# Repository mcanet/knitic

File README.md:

Knitic
======

This software is part of the first open hardware knitting machine project, at the moment based on old electronic Brother knitting machines. 

Here we are testing with KH930, KH940, but we will work with any Digital Brother Knitting machine. 

We have developed in an artist residency at Marginalia+Lab in Belo Horizonte (Brazil) and Constant(Belgium). 
There is more information on the project website: http://knitic.com

Authors: Varvara Guljajeva(http://varvarag.info) and Mar Canet (http://mcanet.info). We are a couple of new media artist that we like to build our own tools.

We have publish some articles about this topic:
- Knitic - The Revolution of Soft Digital Fabrication. DH 2013: 497-499 [http://dh2013.unl.edu/abstracts/ab-173.html]

The project copyright with GNU-GPL: http://es.wikipedia.org/wiki/GNU_General_Public_License

Any questions please send to: mar.canet@gmail.com

> THIS MATERIAL IS DISTRIBUTED AS IS WITH NO GUARANTEE OF FUNCTIONALITY OR RELEVANCE TO THIRD PARTY PROJECTS - THE DEVELOPERS ARE THUS NOT TO BE HELD RESPONSIBLE FOR PERSONAL INJURIES, HARDWARE, FINANCIAL, OR ANY OTHER LOSSES AND IN GENERAL FOR ANY MISFORTUNATE EVENT CAUSED BY THE DESCRIBED SOFTWARE/HARDWARE OR IN THE PROCESS OF ATTEMPTING TO IMPLEMENT IT. IF YOU DON'T AGREE WITH THE AFOREMENTIONED YOUR ARE NOT ALLOWED TO USE THE MATERIAL PROVIDED HEREIN

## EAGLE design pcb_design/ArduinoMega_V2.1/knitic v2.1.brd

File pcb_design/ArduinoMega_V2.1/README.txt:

README Knitic v2.1 - 09/2015
Fablab Wellington
Zoilo ABAD

Changes :
-Eagle files
-improvement with smd component
-selectable 5V or 3.3V
-inboard resistor for optoswitch

-add a adapter board for KH-970 connector

choice the right resistor for the optoswitch you have and the voltage you have.

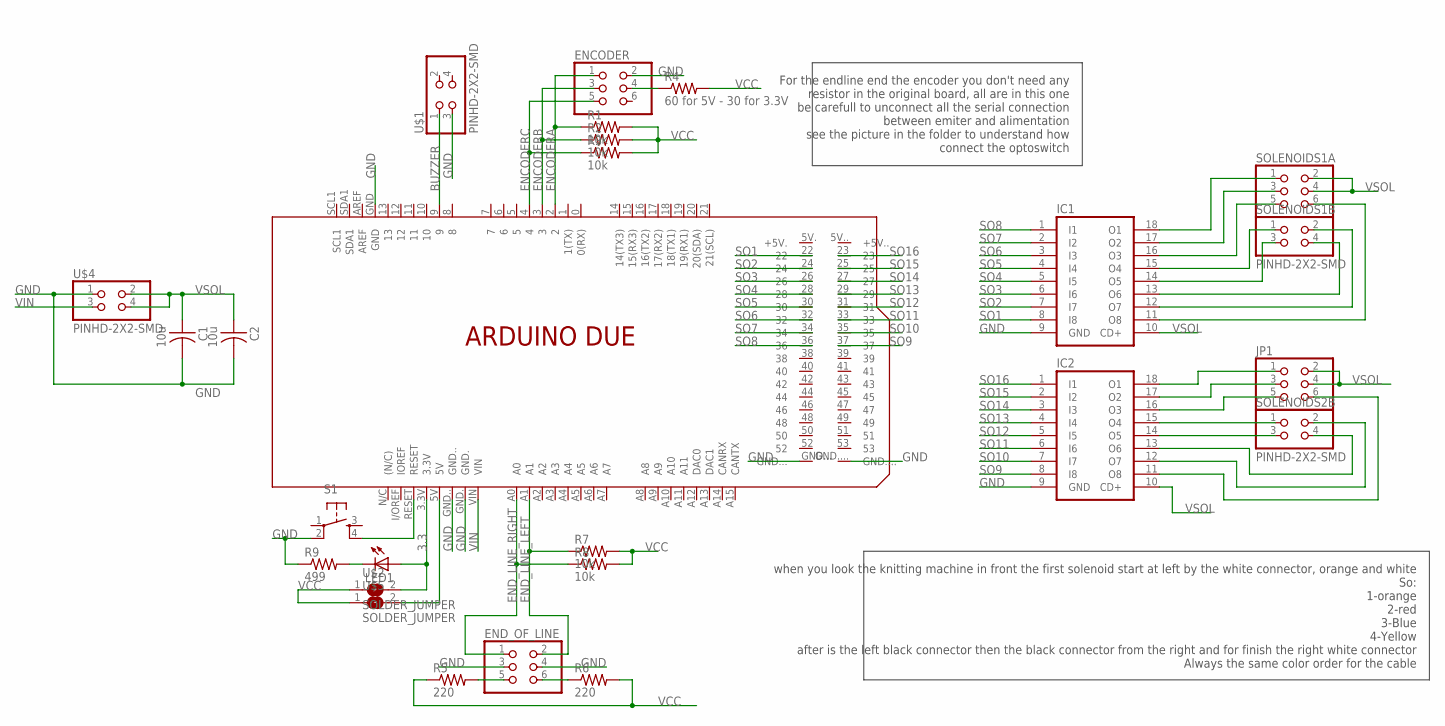
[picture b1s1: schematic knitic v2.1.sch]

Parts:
C1, C2: 10u; C1206FAB
ENCODER: PINHD-2X3-SMD; 2X03SMD
END_OF_LINE: PINHD-2X3-SMD; 2X03SMD
IC1, IC2: ULN2803ASO; SO18W
JP1: PINHD-2X3-SMD; 2X03SMD
LED1: LEDSMT1206; 1206
PCB1: ARDUINO_DUE_MIN
R1, R2, R3, R7, R8: 10k; R1206FAB
R4: 60 for 5V - 30 for 3.3V; R1206FAB
R5, R6: 220; R1206FAB
R9: 499; R1206FAB
S1: 6MM_SWITCH6MM_SWITCH; 6MM_SWITCH
SOLENOIDS1A: PINHD-2X3-SMD; 2X03SMD
SOLENOIDS1B, SOLENOIDS2B: PINHD-2X2-SMD; 2X02SMD
U$1, U$4: PINHD-2X2-SMD; 2X02SMD
U$2, U$5: SOLDER_JUMPER; SJFAB

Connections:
3.3: LED1.A, PCB1.3.3V, U$2.2
BUZZER: PCB1.9, U$1.1
ENCODERA: ENCODER.1, PCB1.2, R1.1
ENCODERB: ENCODER.3, PCB1.3, R2.1
ENCODERC: ENCODER.5, PCB1.4, R3.1
END_LINE_LEFT: END_OF_LINE.2, PCB1.A1, R7.1
END_LINE_RIGHT: END_OF_LINE.1, PCB1.A0, R8.1
GND: C1.2, C2.2, ENCODER.2, END_OF_LINE.3, END_OF_LINE.4, IC1.9 (GND), IC2.9 (GND), PCB1.GND, PCB1.GND., PCB1.GND.., R9.1, S1.2 (P1), U$1.3, U$4.1
unnamed: ENCODER.4, R4.1
unnamed: END_OF_LINE.5, R5.2
unnamed: PCB1.RESET, S1.4 (S1)
unnamed: IC1.18 (O1), SOLENOIDS1A.1
unnamed: END_OF_LINE.6, R6.1
unnamed: LED1.C, R9.2
unnamed: IC1.17 (O2), SOLENOIDS1A.3
unnamed: IC1.16 (O3), SOLENOIDS1A.5
unnamed: IC1.15 (O4), SOLENOIDS1B.1
unnamed: IC1.14 (O5), SOLENOIDS1B.3
unnamed: IC1.13 (O6), SOLENOIDS1B.4
unnamed: IC1.12 (O7), SOLENOIDS1B.2
unnamed: IC1.11 (O8), SOLENOIDS1A.6
unnamed: IC2.18 (O1), JP1.1
unnamed: IC2.12 (O7), SOLENOIDS2B.2
unnamed: IC2.17 (O2), JP1.3
unnamed: IC2.16 (O3), JP1.5
unnamed: IC2.13 (O6), SOLENOIDS2B.4
unnamed: IC2.15 (O4), SOLENOIDS2B.1
unnamed: IC2.11 (O8), JP1.6
unnamed: PCB1.5V, U$5.2
unnamed: IC2.14 (O5), SOLENOIDS2B.3
SO1: IC1.8 (I8), PCB1.22
SO2: IC1.7 (I7), PCB1.24
SO3: IC1.6 (I6), PCB1.26
SO4: IC1.5 (I5), PCB1.28
SO5: IC1.4 (I4), PCB1.30
SO6: IC1.3 (I3), PCB1.32
SO7: IC1.2 (I2), PCB1.34
SO8: IC1.1 (I1), PCB1.36
SO9: IC2.8 (I8), PCB1.37
SO10: IC2.7 (I7), PCB1.35
SO11: IC2.6 (I6), PCB1.33
SO12: IC2.5 (I5), PCB1.31
SO13: IC2.4 (I4), PCB1.29
SO14: IC2.3 (I3), PCB1.27
SO15: IC2.2 (I2), PCB1.25
SO16: IC2.1 (I1), PCB1.23
VCC: R1.2, R2.2, R3.2, R4.2, R5.1, R6.2, R7.2, R8.2, U$2.1, U$5.1
VIN: PCB1.VIN, U$4.3
VSOL: C1.1, C2.1, IC1.10 (CD+), IC2.10 (CD+), JP1.2, JP1.4, SOLENOIDS1A.2, SOLENOIDS1A.4, U$4.2, U$4.4

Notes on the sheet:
when you look the knitting machine in front the first solenoid start at left by the white connector, orange and white So: 1-orange 2-red 3-Blue 4-Yellow after is the left black connector then the black connector from the right and for finish the right white connector Always the same color order for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
For the endline end the encoder you don't need any resistor in the original board, all are in this one be carefull to unconnect all the serial connection between emiter and alimentation see the picture in the folder to understand how connect the optoswitch

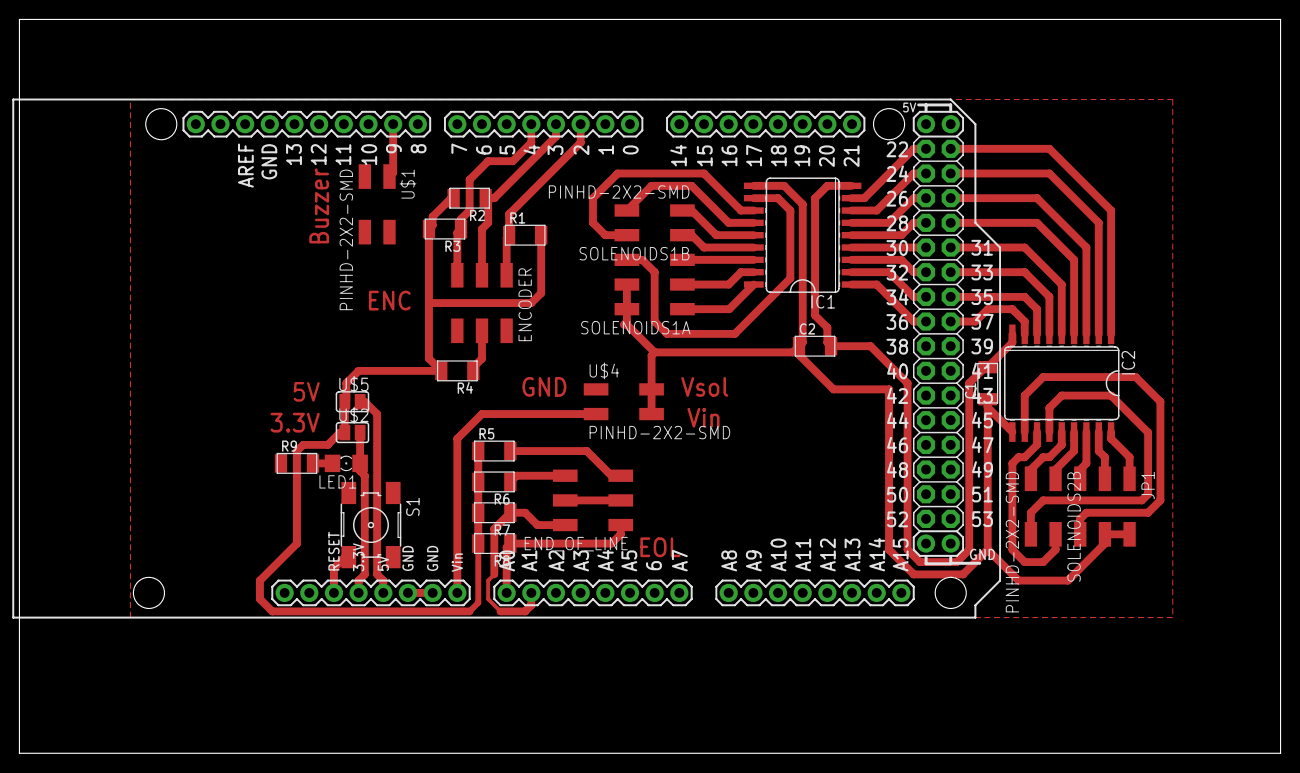
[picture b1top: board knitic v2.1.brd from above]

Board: 2 copper layers, 129.8 x 75.6 mm, 26 parts (0 on the bottom side), 49 nets.

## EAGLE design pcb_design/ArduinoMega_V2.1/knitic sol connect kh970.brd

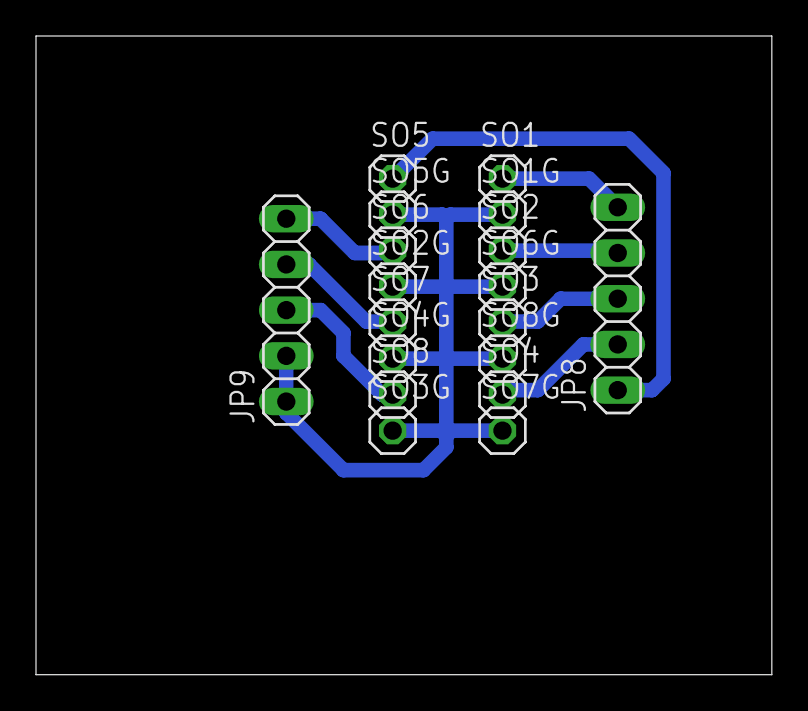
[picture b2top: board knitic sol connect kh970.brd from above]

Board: 2 copper layers, 40.9 x 35.5 mm, 18 parts (0 on the bottom side), 9 nets.

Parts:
JP8, JP9: 1X05
SO1, SO1G, SO2, SO2G, SO3, SO3G, SO4, SO4G, SO5, SO5G, SO6, SO6G, SO7, SO7G, SO8, SO8G: 1X01

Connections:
unnamed: JP9.3, SO8.1
unnamed: JP9.4, SO7.1
unnamed: JP8.1, SO5.1
unnamed: JP8.5, SO1.1
unnamed: JP8.4, SO2.1
unnamed: JP8.3, SO3.1
unnamed: JP8.2, SO4.1
unnamed: JP9.1, JP9.2, SO1G.1, SO2G.1, SO3G.1, SO4G.1, SO5G.1, SO6G.1, SO7G.1, SO8G.1
SO6G: JP9.5, SO6.1

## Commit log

2012-10-20 test first code
2012-10-20 add arduino code
2012-10-20 update code
2012-10-20 fix communication
2012-10-20 working send serial to selenoids
2012-10-21 Fixed "Refresh Serial Port" Button
2012-10-21 fix gui layout and function signatures
    - using new function signature for ofxUILabelButton
    - simplify gui layout using variables
2012-10-21 fixing gui directory (all uppercase!)
2012-10-21 comment out empty action_gui
    - action_gui is not used right now
    - empty gui object may cause crash on exit
2012-10-22 last code from knitic
2012-10-22 add prototype in processing for app
2012-10-22 add pull from craftoid
2012-10-22 I think this is a bug. This extra - will make the comparisons always evaluate to false
2012-10-23 rename sketch p5
2012-10-23 last
2012-10-23 new things
2012-10-23 add scrollbar.pde
2012-10-23 add alerts
2012-10-23 add grid to display pattern
2012-10-23 fixed receiveSerial function
2012-10-23 fix connected status to arduino
2012-10-23 fixed serial connection detection
2012-10-23 arduino code update
2012-10-23 correct mar website
2012-10-23 fix direction sensor with encoders
2012-10-23 fix absolute position encoders
2012-10-23 commend unnecesary serial prints
2012-10-24 improve serial communication
2012-10-24 improve code
2012-10-24 fix tons errors
2012-10-24 timer in sender
2012-10-24 started figuring out arduino serial receive
2012-10-25 new stuff
2012-10-25 new way for serial read
2012-10-25 receive serial is working
2012-10-25 small changes to make arduino serial receive work
2012-10-25 cleaned up formatting differences
2012-10-26 pixel to selenoid done
2012-10-26 autoformat
2012-10-26 add repeat pattern
2012-10-26 aesthetic changes to code... removed some empty lines...
2012-10-26 auto-formatting
2012-10-26 add go to a row
2012-10-26 aesthetic cleanup
2012-10-26 fixing shift-reg output. latch signal was missing.
2012-10-27 cleaned up some of the shift-register code
2012-10-27 enabled all loops
2012-10-27 code cleanup: removed a serial.print and cleanup up some comments
2012-10-27 added small delay between data update and clock to remove flickering of output
2012-10-27 trying to fix register outputs
2012-10-27 last row is now first to be knit
2012-10-28 add visualization to head position
2012-10-28 change to serial send to 115200 bauds
2012-10-28 change serial rate to 115200
2012-10-28 change b position to d
2012-10-28 fix back to front knitting
2012-10-28 further fixing shift register flicker
2012-10-29 trying to get cart position from encoder readings
2012-10-29 added code to receive stitch value from arduino/serial
2012-10-29 removed unecessary print
2012-10-29 trying to fix encoder reading values
2012-10-29 still trying to fix encoder reading values... taking care of end cases...
2012-10-29 trying to get rid of crashes on quit. this seems to be one problem
2012-10-29 autoformated processing
2012-10-29 nothing just to avoid conflict
2012-10-29 auto-format
2012-10-29 removed mystery counter code
2012-10-29 small change: check stitch variable before using stitch variable
2012-10-30 encoders change 4 times per needle. hacks to account for that.
2012-10-30 small code cleanup
2012-11-02 fix starting state error
2012-11-02 add some stich simulation keys
2012-11-02 add visualization 16 current stitch
2012-11-02 right order of selenoids
2012-11-03 change start knidle from left to right. Now right site have knidle 0 and left 200
2012-11-04 update code from change origin to right
2012-11-04 fix solenoids display
2012-11-04 Optimization drawing pixel
2012-11-05 Add compatiblity for big images
2012-11-05 fix rotation image
2012-11-05 try to catch exceptions in open file
2012-11-05 disable sections
2012-11-05 add stich correct
2012-11-05 take out some anoying print
2012-11-07 add new update method for solenoids per knitch by knitch
2012-11-07 renaming variables selenoids to Solenoids - some spelling mistakes
2012-11-12 changed selenoid to solenoid in variable names
2012-11-13 last code
2012-11-19 last updates
2012-11-19 sort global variables
2012-11-21 fix movement heads left right with 32 offset
2012-11-21 add start left and right side
2012-11-21 add reset status
2012-11-21 shiftout timing and improve update selenoids
2012-11-21 removed .DS files
2012-11-21 change receive and send
2012-11-21 add mega code to control selenoids
2012-11-21 trying to fix comunication between arduino and processing, Processing misses some messages.
2012-11-21 receive
2012-11-21 add states for knitting
2012-11-22 improve efficiency and compatibilty to mega
2012-11-22 fix spelling mistake with selenoids to solenoids
2012-11-22 last code processing
2012-11-22 reduce for innecessary
2012-11-23 experimental shiftOut
2012-12-01 ADADA
2013-01-22 asdasd
2013-03-07 fix mapping solenoids
2013-03-09 fix left and right direction label
2013-03-09 fix array solenoids
2013-03-09 fix 16 solenoid visualization
2013-03-11 fix 16 solenoid visual selector. Add color to direction
2013-03-14 fix left and right direction to apply pattern to solenoids. Also simplify code
2013-03-17 fix hotplugging usb, left placing pattern, mirror pattern, handling big patterns, handling small with patterns
2013-03-18 clear code, add nicer font,fix edit pixels
2013-03-18 change not defined knidles from contrast yarn
2013-03-18 fix hoting solenoids, and warning when head is left in middle
2013-03-28 add PCB design
2013-03-29 Handle encoders with a state machine
    Differences between the old and new encoder methods:
    Old code used string compares, New code uses an arrary lookup
    Old code:
    1. Tracked each change in the encoder signals
    as a movement in a direction
    2. Accepted two movements in the same direction as
2013-04-01 add comunication improved with 2char bit encoded the 16 solenoids
2013-04-01 back to code without steve merge
2013-04-01 clean code and fix serial send
2013-04-01 clean more code
2013-04-01 add new more efficient encoder code not using strings instead shorts
2013-04-01 deleting arduino_code/openKnitting_handMadepcb_v0_1/openKnitting_handMadepcb_v0_1.pde
2013-04-04 disconected more timeout
2013-04-04 fix odd small patterns
2013-04-14 separated class in files to improve code readability
2013-04-17 update selenoids
2013-04-19 add current stich selection and visualization. It is a important new step.
2013-04-25 new version send all line
2013-05-03 new PCB design for ArduinoDue
2013-05-03 jpg from PCB design
2013-05-07 700 heigh version
2013-05-07 chech encoderC
2013-05-08 add application mac,pc, linux
2013-05-12 shift sections
2013-05-18 add before workshop early adopters
2014-01-05 last updates
    - delete old OF app (never used)
    - update processing code
2014-01-06 1layer PCB design. missing custom-made power connector
2014-01-08 adding compatibility to OpenKnit machine
2014-01-14 New features openKnit
2014-01-14 more options openKnit
2014-01-15 better and bigger title parametric sweater
2014-01-15 take out debug variables
2014-01-15 last update
2014-01-15 buttons bigger
2014-01-17 add fonts
2014-01-17 fix error
2014-03-01 fix errors
2014-03-02 Add feature double bed - two Colours
    Exported new app for macox windows soon
2014-03-03 fix test send line test
    fix test_send line to correct speed serial to 115200
2014-05-10 new pcb with jumper
    This redesign by Lucas Bahle and Kanno So. This one can alternative
    power from Vin of Arduino solenoids.
2015-08-10 test endlines to calibrate
2015-08-11 add test to detect belt shift
    if this works rest works like charm
2015-08-11 add console for belt shift
2015-08-11 belt shift change
2015-09-09 sdrop bug
    doesn't support by processing 3.0
2015-09-09 compatibilities 2.2.1
    visual arrangement and compatibilities with processing 2.2.1
2015-09-09 change dropdownlist to scrollablelist
2015-09-09 change usb detection
2015-09-09 change controlevent to match with the scrollablelist
2015-09-09 clean and try to make clean scrollablelist
2015-09-10 scrollable list update
    change the way to catch the result of scrollable list
2015-09-10 finish to change scrollable list usage
    clean all error and malfonction of scrollable list
2015-09-10 Compatibilitie with Mega and Uno interrupt
    change the interupt fonction
2015-09-11 add new version of pcb design in eagle
    new pcb and breakout board for the kh-970
2015-09-13 Add info and reset/led on pcb design
2015-09-14 export windows executable
2015-09-14 end line for more compatibilities
    changing filter value
2015-09-16 add refresh usb list button
2015-09-16 try to understand the error in pixel
2015-09-17 clean and error pixel solution search
2015-09-17 no more error in pixel
    fixe the error in pixel, try to access inexistante position on the array
    : pixelArray
2015-09-17 Fix error on corrupt data
    If you send and recieve the data inside the interrupt it is only when
    you move so more interrupt and corrupt data for the future
    if it is outside the interrupt that can be do when you don't move
2015-09-18 Clean and new solenoid test
    some clean of old code, new solenoid test to check one by one
2015-09-20 fix beltshift
2015-09-20 Filter values need to be regulated in each machine
    Added instructions
2015-09-20 fix last commit preprocessors position
2015-09-21 lots of clean in arduino, solenoids close to be fix
    - merge the fork of kinasmith to fix the solenoid glitch, close to the
    solution!!
    - clean all the unused variable and use more the defined_knitic.
    - delete the zip source to less weight
2015-09-21 clean processing
2015-09-21 clean end and export windows-linux
    clean end of all arduino and processing part
    export executable except macos because i can't
2015-09-21 clean code and add license GPL in file INO
2015-09-21 Try to use the phase for the kh930-940
    To try with all machine
2015-09-22 Machine type selection, offset settings
    machine type selection for 970 or 940
    offset to be set to match of the model(good settings for the 970)
2015-09-25 control transfert, release solenoids, less glitch
    - control transfert to detect corrupt data
    - release solenoids when no connection
    - less glitch at the extremity
2015-09-25 Add a port.clear() before receive check of the pixels
    This avoid many double checks
2015-09-29 add mac ox export
2015-09-30 Add Debug console
2015-10-01 clean macosx, speed R/W, try to port to 3.0
    don't export the java file when export macos app
    Direct read write try
    new project for processing 3.0
2015-11-22 Update README.md
    two small grammar corrections
